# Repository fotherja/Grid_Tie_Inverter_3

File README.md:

# Grid_Tie_Inverter_3
Software and Hardware for GTI v3

Here the software and hardware files for the Grid Tie inverter project I'm working on. This is version 3. More to come soon.

I use STMCubeIDE for the software developer. I have used the CMSIS DSP library to do FFTs

I used Kicad to design the PCBs and the files are included here too

I'm working on a writeup - not quite finished yet.

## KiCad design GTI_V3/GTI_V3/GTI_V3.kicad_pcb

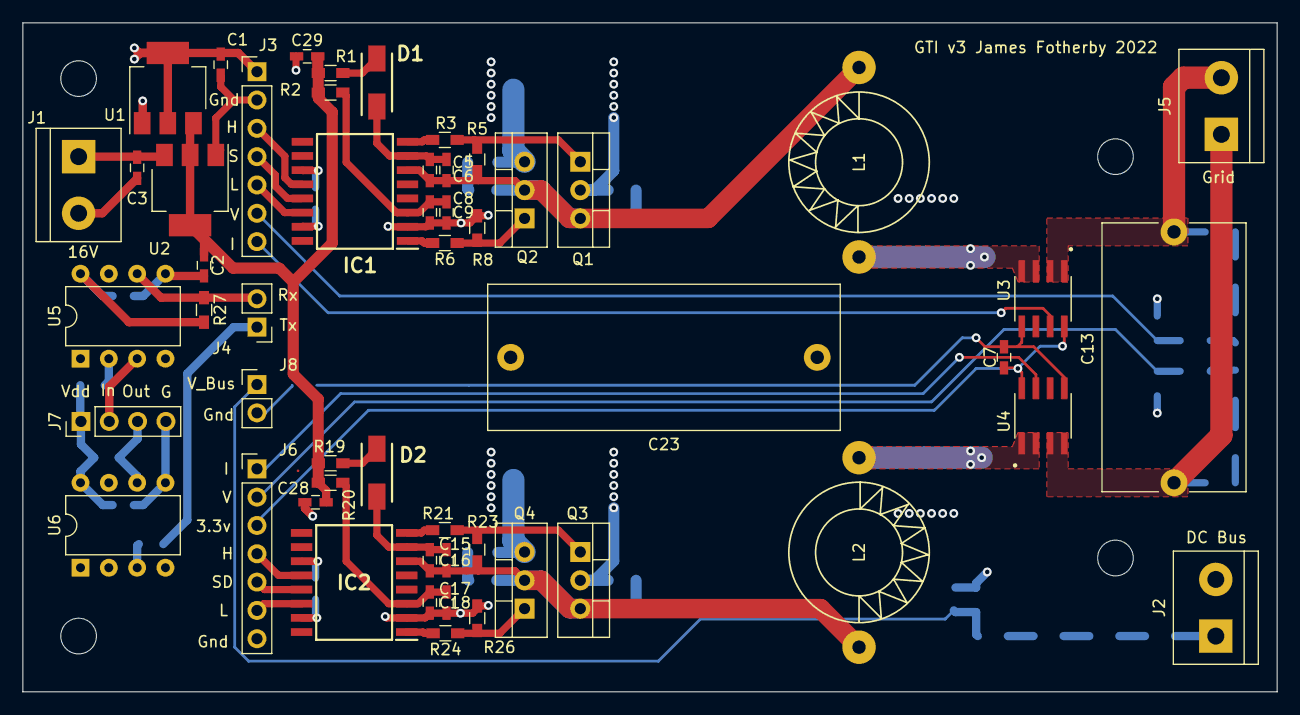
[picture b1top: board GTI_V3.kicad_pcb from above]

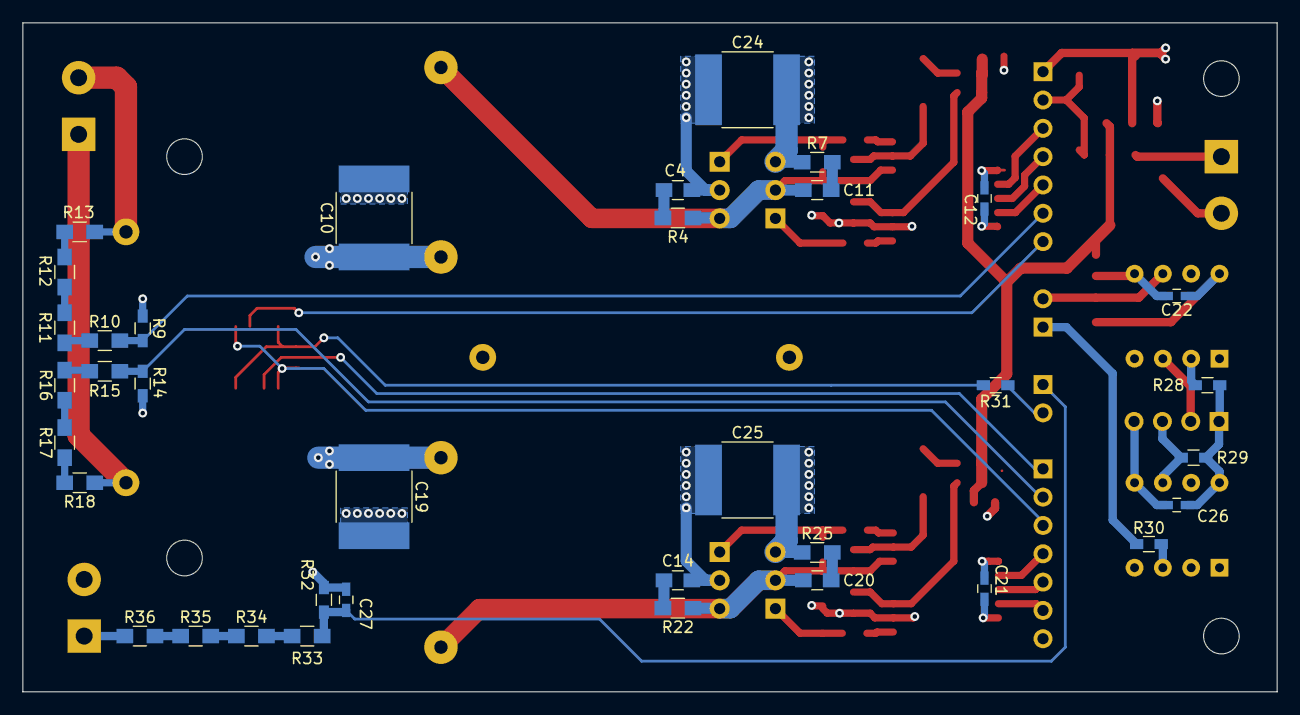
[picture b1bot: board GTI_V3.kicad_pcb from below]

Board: 4 copper layers, 112.5 x 60.0 mm, 89 parts (36 on the bottom side), 58 nets.

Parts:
C1, C2, C3: 10uF; C_0603_HandSoldering
C4, C11, C14, C20: 22pF; C_0805_HandSoldering
C5, C7, C8, C12, C15, C17, C21, C22, C26, C28, C29: 100nF; C_0603_HandSoldering
C6, C9, C16, C18: 2.2uF; C_0603_HandSoldering
C10, C19: C; C_2225_HandSoldering
C13: 2uF; C_Rect_L24.0mm_W12.8mm_P22.50mm_MKT
C23: 10uF; C_Rect_L31.5mm_W13.0mm_P27.50mm_MKS4
C24, C25: 0.47uF; C_2225_HandSoldering
C27: 10nF; C_0603_HandSoldering
D1, D2: ES1J; DIOM5227X250N
IC1, IC2: DGD2110S16-13; SOIC127P1032X264-16N
J1, J2, J5: Screw_Terminal_01x02; TerminalBlock_bornier-2_P5.08mm
J3, J6: Conn_01x07_Male; Socket_Strip_Straight_1x07_Pitch2.54mm
J4, J8: Conn_01x02_Male; Socket_Strip_Straight_1x02_Pitch2.54mm
J7: Conn_01x04_Male; Socket_Strip_Straight_1x04_Pitch2.54mm
L1, L2: L; Choke_Toroid_horizontal_Diameter12-5mm_Amidon-T44
Q1, Q2, Q3, Q4: STF35N60DM2; TO-220-3_Vertical
R1, R2, R19, R20: 2.2R; R_0603_HandSoldering
R3, R6, R21, R24: 4.7R; R_0603_HandSoldering
R4, R7, R22, R25: 15R; R_0805_HandSoldering
R5, R8, R23, R26: 10K; R_0603_HandSoldering
R9, R14, R32: 2.2K; R_0603_HandSoldering
R10, R11, R12, R13, R15, R16, R17, R18, R33, R34, R35, R36: 100K; R_0805_HandSoldering
R27, R29: 470R; R_0603_HandSoldering
R28, R30: 330R; R_0603_HandSoldering
R31: 0R; R_0603_HandSoldering
U1: NCP1117-3.3_SOT223; SOT-223-3_TabPin2
U2: NCP1117-12_SOT223; SOT-223-3_TabPin2
U3, U4: ACS722LLCTR-05AB-T; SOIC127P600X175-8N
U5, U6: 6N137; DIP-8_W7.62mm

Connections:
+3V3: C1.1, C7.1, C12.1, C21.1, C22.1, IC1.11 (VDD), IC2.11 (VDD), J3.1, J6.3, R27.2, U1.2 (VO), U3.8 (VCC), U4.8 (VCC), U5.8 (VCC), U6.2 (A)
+12V: C2.1, C28.1, C29.1, R1.2, R2.2, R19.2, R20.2, U1.3 (VI), U2.2 (VO)
/Ext_Gnd: C26.2, J7.4, U6.5 (GND)
/Ext_Rx: J7.3, R29.1, U6.6 (VO)
/Ext_Tx: J7.2, U5.3 (C)
/Ext_Vdd: C26.1, J7.1, R28.2, R29.2, U6.8 (VCC)
/I_Sense_A: J3.7, U3.7 (VIOUT)
/I_Sense_B: J6.1, U4.7 (VIOUT)
/Rx: J4.2, R27.1, U5.6 (VO)
/Tx: J4.1, R30.1
/VBUS_Sense: C27.1, J8.1, R32.2, R33.2
/V_Sense_A: J3.6, R9.2, R10.2
/V_Sense_B: J6.2, R14.2, R15.2
GND: C1.2, C2.2, C3.2, C8.2, C9.2, C10.2, C12.2, C17.2, C18.2, C19.2, C21.2, C22.2, C23.2, C24.2, C25.2, C27.2, C28.2, C29.2, IC1.2 (COM), IC1.15 (VSS), IC2.2 (COM), IC2.15 (VSS), J1.2, J2.2, J3.2, J6.7, J8.2, Q2.3 (S), Q4.3 (S), R7.1, R8.2, R9.1, R14.1, R25.1, R26.2, R31.1, R32.1, U1.1 (GND), U2.1 (GND), U5.5 (GND)
GNDA: C7.2, R31.2, U3.5 (GND), U4.5 (GND)
unnamed: C4.2, R4.2
unnamed: C5.1, C6.1, D1.1, IC1.7 (VB)
unnamed: C8.1, C9.1, IC1.3 (VCC), R2.1
unnamed: C10.1, L1.2, U3.3 (IP-), U3.4 (IP-)
unnamed: C5.2, C6.2, C11.1, IC1.6 (VS), L1.1, Q1.3 (S), Q2.2 (D), R4.1, R5.2
unnamed: C11.2, R7.2
unnamed: C13.1, J5.2, R13.1, U3.1 (IP+), U3.2 (IP+)
unnamed: C13.2, J5.1, R18.1, U4.3 (IP-), U4.4 (IP-)
unnamed: C14.2, R22.2
unnamed: C15.1, C16.1, D2.1, IC2.7 (VB)
unnamed: C15.2, C16.2, C20.1, IC2.6 (VS), L2.1, Q3.3 (S), Q4.2 (D), R22.1, R23.2
unnamed: C17.1, C18.1, IC2.3 (VCC), R20.1
unnamed: C19.1, L2.2, U4.1 (IP+), U4.2 (IP+)
unnamed: C20.2, R25.2
unnamed: D1.2, R1.1
unnamed: D2.2, R19.1
unnamed: IC1.1 (LO), R6.2
unnamed: IC1.8 (HO), R3.2
unnamed: IC1.12 (HIN), J3.3
unnamed: IC1.13 (SD), J3.4
unnamed: IC1.14 (LIN), J3.5
unnamed: IC2.1 (LO), R24.2
unnamed: IC2.8 (HO), R21.2
unnamed: IC2.12 (HIN), J6.4
unnamed: IC2.13 (SD), J6.5
unnamed: IC2.14 (LIN), J6.6
unnamed: Q1.1 (G), R3.1, R5.1
unnamed: Q2.1 (G), R6.1, R8.1
unnamed: Q3.1 (G), R21.1, R23.1
unnamed: Q4.1 (G), R24.1, R26.1
unnamed: R10.1, R11.2
unnamed: R11.1, R12.2
unnamed: R12.1, R13.2
unnamed: R15.1, R16.2
unnamed: R16.1, R17.2
unnamed: R17.1, R18.2
unnamed: R28.1, U5.2 (A)
unnamed: R30.2, U6.3 (C)
unnamed: R33.1, R34.2
unnamed: R34.1, R35.2
unnamed: R35.1, R36.2
VBUS: C4.1, C14.1, C23.1, C24.1, C25.1, J2.1, Q1.2 (D), Q3.2 (D), R36.1
VCC: C3.1, J1.1, U2.3 (VI)

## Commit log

2022-09-11 Add files via upload
    core software uploaded and the CMSIS math library for DSP
